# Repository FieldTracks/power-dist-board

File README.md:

# power-dist-board
Power Distribution Board - experimental design

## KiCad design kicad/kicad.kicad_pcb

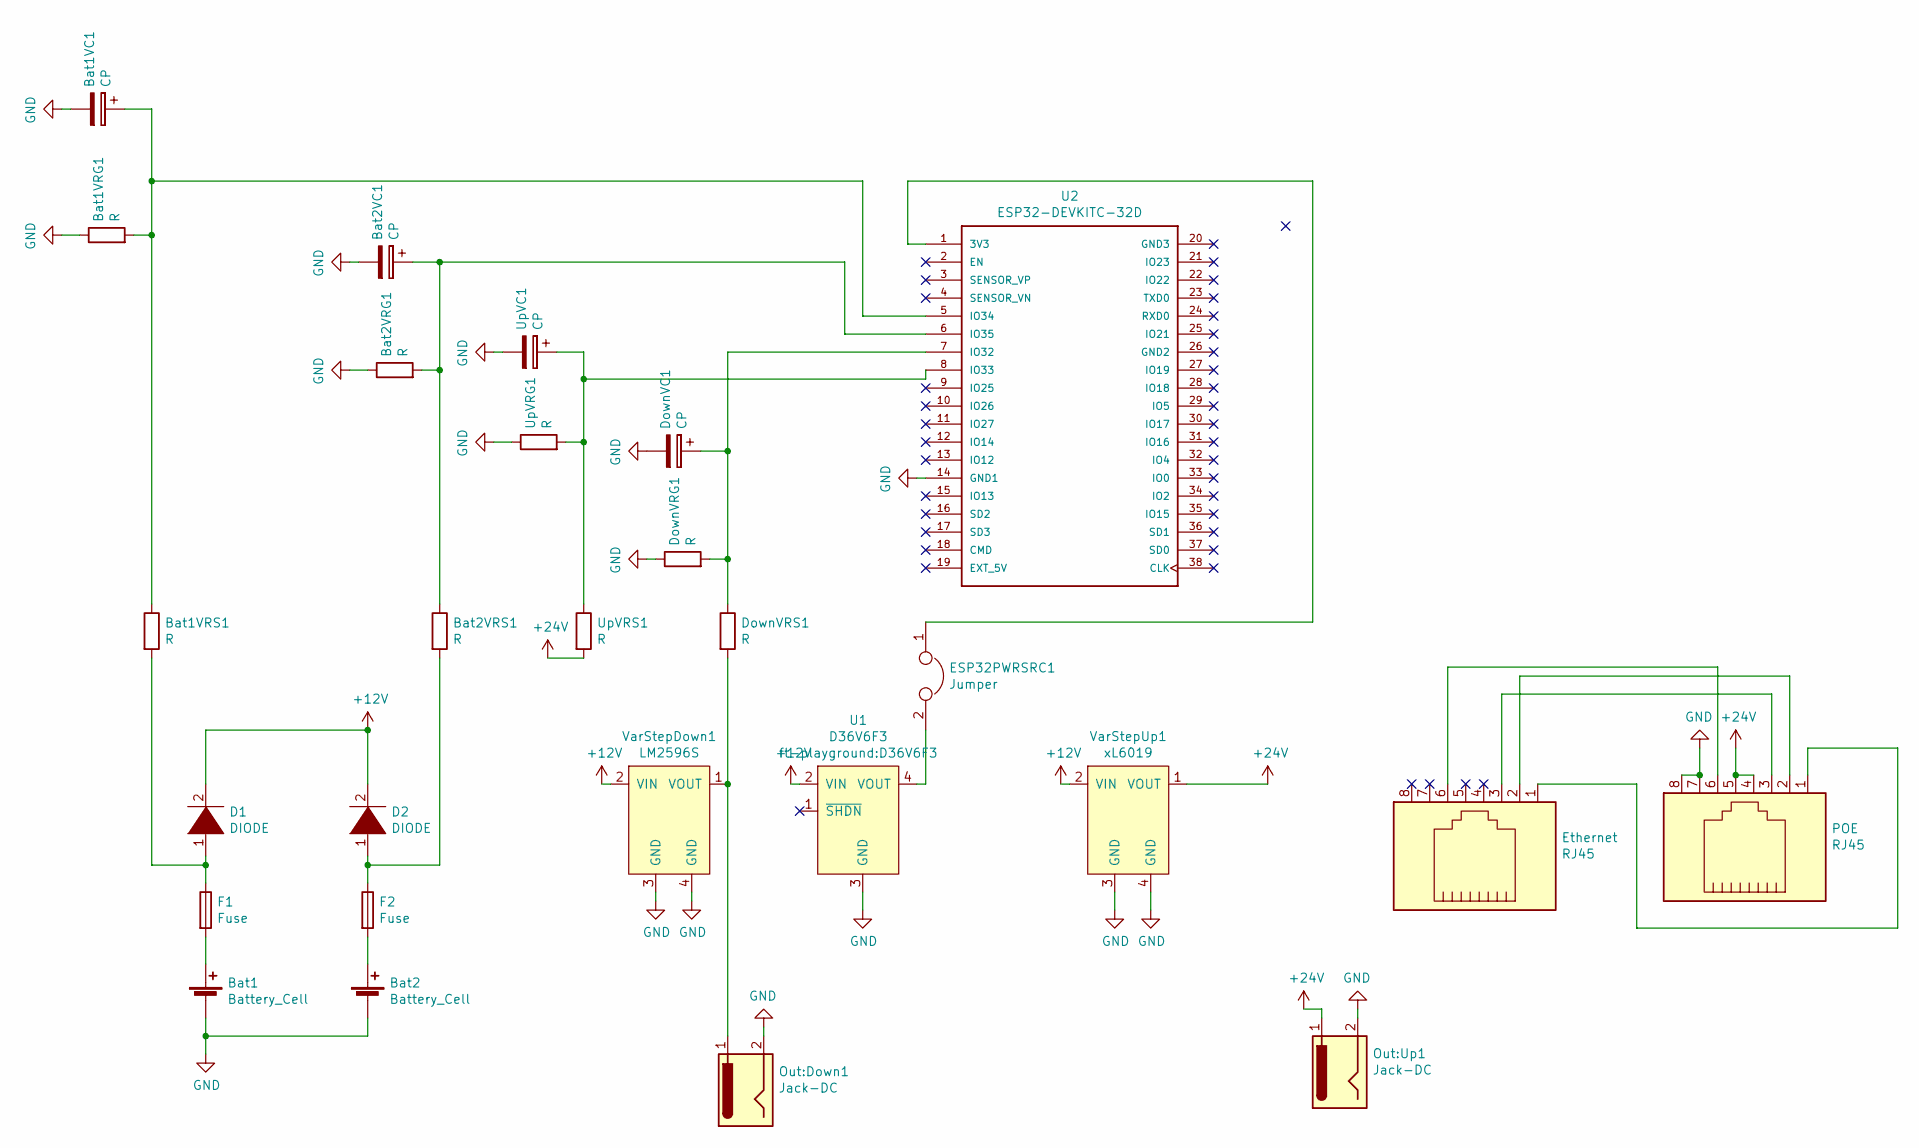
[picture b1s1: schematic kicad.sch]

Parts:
Bat1, Bat2: Battery_Cell; BarrelJack_Horizontal
Bat1VC1, Bat2VC1: CP; C_1806_4516Metric_Pad1.57x1.80mm_HandSolder
Bat1VRG1, Bat1VRS1, Bat2VRG1, Bat2VRS1: R; R_1210_3225Metric_Pad1.42x2.65mm_HandSolder
D1, D2: DIODE; D_DO-15_P5.08mm_Vertical_AnodeUp
DownVC1: CP; C_1806_4516Metric_Pad1.57x1.80mm_HandSolder
DownVRG1: R; R_1210_3225Metric_Pad1.42x2.65mm_HandSolder
DownVRS1: R; R_1210_3225Metric_Pad1.42x2.65mm_HandSolder
ESP32PWRSRC1: Jumper; PinHeader_1x02_P2.54mm_Vertical
Ethernet: RJ45; RJ45_Amphenol_54602-x08_Horizontal
F1, F2: Fuse; Fuse_Bourns_MF-RG400
Out:Down1: Jack-DC; BarrelJack_Horizontal
Out:Up1: Jack-DC; BarrelJack_Horizontal
POE: RJ45; RJ45_Amphenol_54602-x08_Horizontal
U1: D36V6F3
U2: ESP32-DEVKITC-32D; MODULE_ESP32-DEVKITC-32D
UpVC1: CP; C_1806_4516Metric_Pad1.57x1.80mm_HandSolder
UpVRG1: R; R_1210_3225Metric_Pad1.42x2.65mm_HandSolder
UpVRS1: R; R_1210_3225Metric_Pad1.42x2.65mm_HandSolder
VarStepDown1: LM2596S
VarStepUp1: xL6019; XL6019

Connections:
+12V: D1.2 (A), D2.2 (A), U1.2 (VIN), VarStepDown1.2 (VIN), VarStepUp1.2 (VIN)
+24V: Out:Up1.1, POE.4, POE.5, UpVRS1.2, VarStepUp1.1 (VOUT); also elsewhere on the board
GND: Bat1.2 (-), Bat1VC1.2, Bat1VRG1.1, Bat2.2 (-), Bat2VC1.2, Bat2VRG1.1, DownVC1.2, DownVRG1.1, Out:Down1.2, Out:Up1.2, POE.7, POE.8, U1.3 (GND), U2.14 (GND1), UpVC1.2, UpVRG1.1, VarStepDown1.3 (GND), VarStepDown1.4 (GND), VarStepUp1.3 (GND), VarStepUp1.4 (GND); also elsewhere on the board
unnamed: Bat1.1 (+), F1.2
unnamed: Bat1VC1.1, Bat1VRG1.2, Bat1VRS1.1, U2.5 (IO34)
unnamed: Bat1VRS1.2, D1.1 (K), F1.1
unnamed: Bat2.1 (+), F2.2
unnamed: Bat2VC1.1, Bat2VRG1.2, Bat2VRS1.1, U2.6 (IO35)
unnamed: Bat2VRS1.2, D2.1 (K), F2.1
unnamed: DownVC1.1, DownVRG1.2, DownVRS1.1, U2.7 (IO32)
unnamed: DownVRS1.2, Out:Down1.1, VarStepDown1.1 (VOUT)
unnamed: ESP32PWRSRC1.1, U2.1 (3V3)
unnamed: ESP32PWRSRC1.2, U1.4 (VOUT)
unnamed: Ethernet.1, POE.1
unnamed: Ethernet.2, POE.2
unnamed: Ethernet.3, POE.3
unnamed: Ethernet.6, POE.6
unnamed: U2.8 (IO33), UpVC1.1, UpVRG1.2, UpVRS1.1

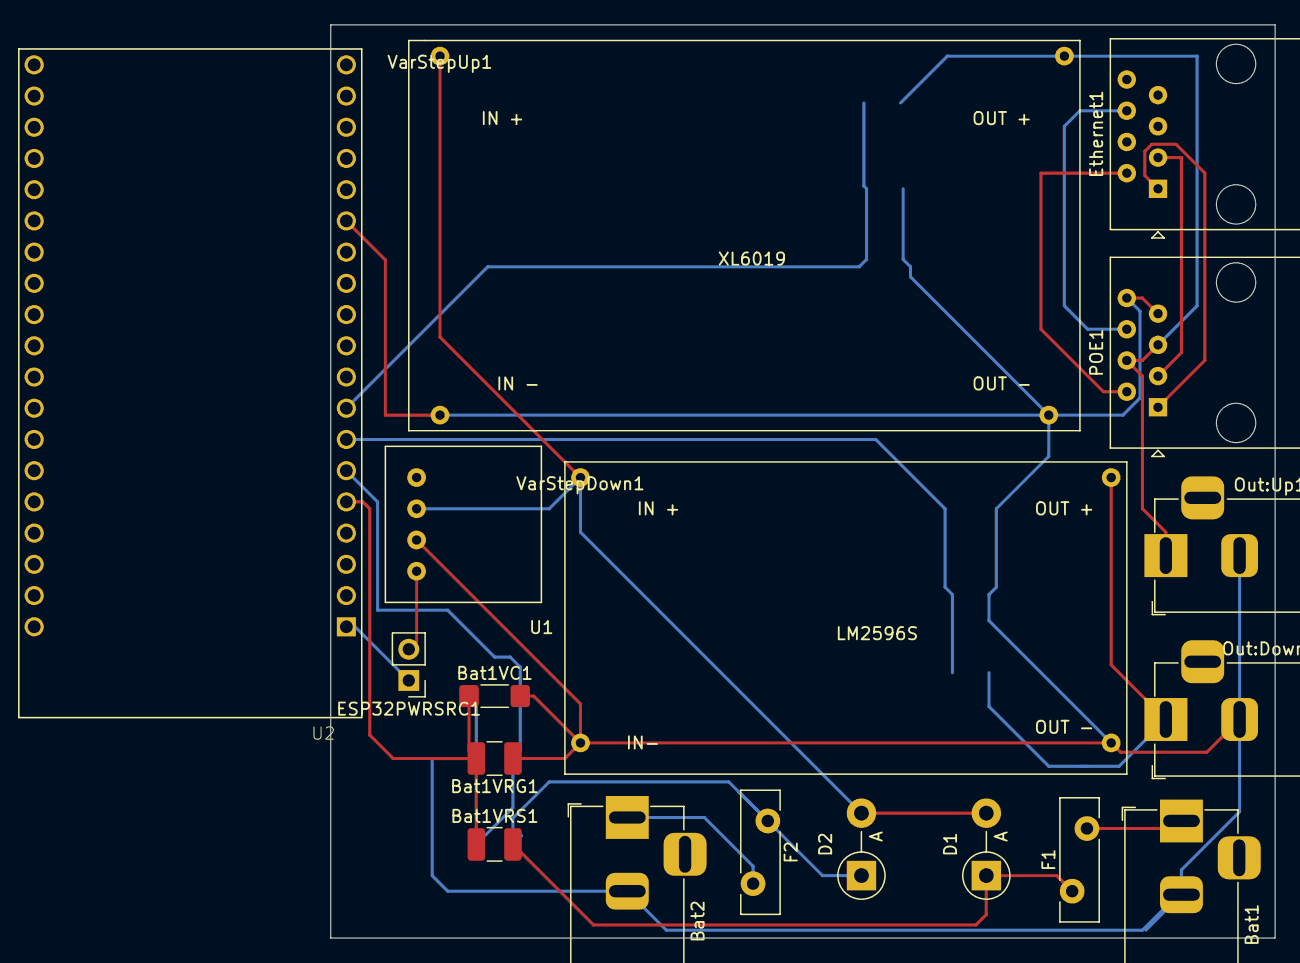
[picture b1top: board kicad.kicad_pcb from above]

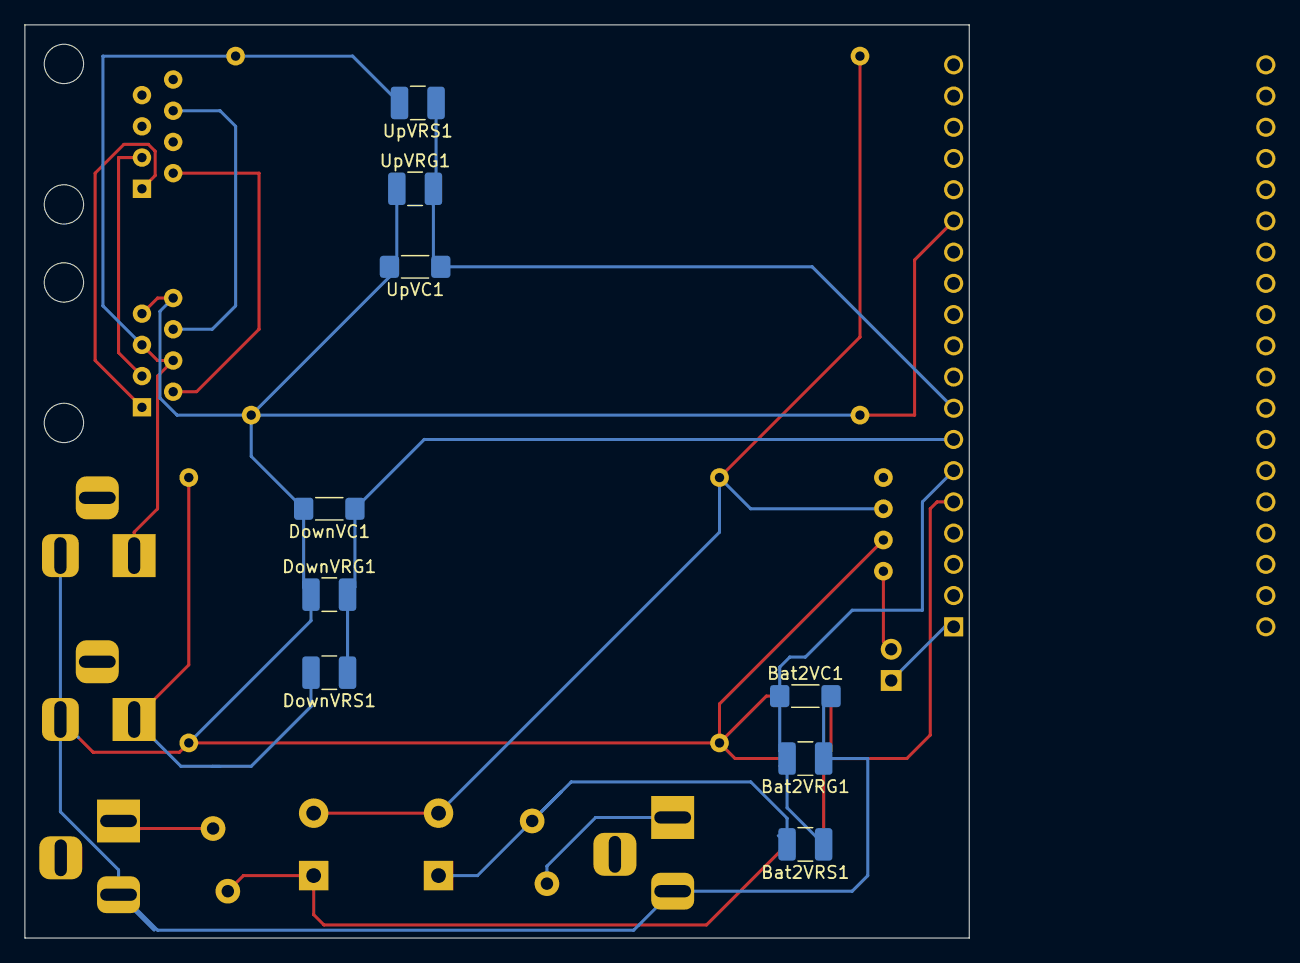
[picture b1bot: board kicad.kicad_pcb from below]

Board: 2 copper layers, 76.8 x 74.3 mm, 27 parts (9 on the bottom side), 18 nets.

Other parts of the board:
Ethernet1: RJ45; RJ45_Amphenol_54602-x08_Horizontal
POE1: RJ45; RJ45_Amphenol_54602-x08_Horizontal

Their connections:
+24V: POE1.4, POE1.5; also elsewhere on the board
GND: POE1.7, POE1.8; also elsewhere on the board
unnamed: Ethernet1.1, POE1.1
unnamed: Ethernet1.2, POE1.2
unnamed: Ethernet1.3, POE1.3
unnamed: Ethernet1.6, POE1.6

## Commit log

2019-11-21 Initial import
2020-01-01 Remaining components
2020-12-25 Zwischenstand 2020-12-25
2020-12-25 Zwischenstand
2021-04-03 Move symbol libraries into the kicad project folder
2021-04-03 Move symbol libraries into the respective folder
2021-04-03 Fix symbol libraries table
2021-04-03 schem: Improve layout & Re-Annotate the schematics
